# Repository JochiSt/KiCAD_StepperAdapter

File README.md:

# KiCAD_StepperAdapter
Adapter from stepper motor driver to screw terminals. 

Using the pinout of a A4988 module. Basically the pins of 
* step
* dir
* enable
* GND
are connected to a 4 pin screw terminal.

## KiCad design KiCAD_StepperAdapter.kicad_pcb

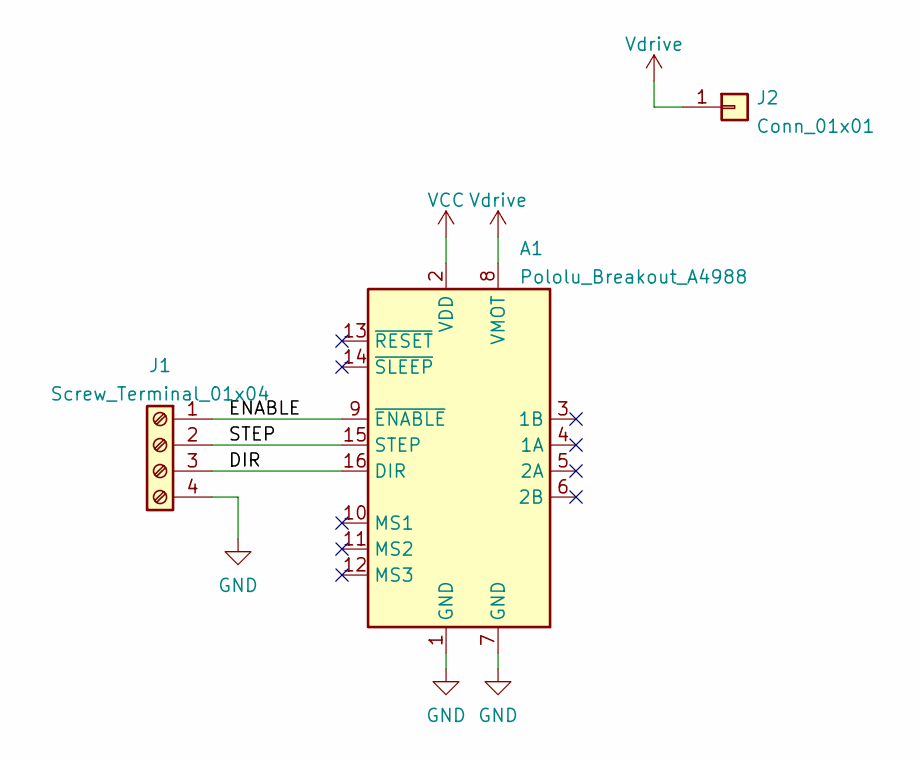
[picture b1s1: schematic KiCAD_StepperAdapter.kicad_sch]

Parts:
A1: Pololu_Breakout_A4988; Pololu_Breakout-16_15.2x20.3mm
J1: Screw_Terminal_01x04; TerminalBlock_Phoenix_MKDS-1,5-4-5.08_1x04_P5.08mm_Horizont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
J2: Conn_01x01; PinHeader_1x01_P2.54mm_Vertical

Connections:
/DIR: A1.16 (DIR), J1.3
/ENABLE: A1.9 (~ENABLE), J1.1
/STEP: A1.15 (STEP), J1.2
GND: A1.1 (GND), A1.7 (GND), J1.4
VCC: A1.2 (VDD)
Vdrive: A1.8 (VMOT), J2.1

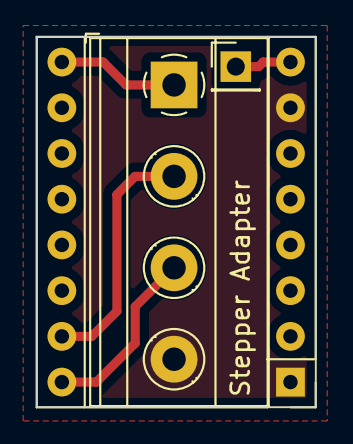
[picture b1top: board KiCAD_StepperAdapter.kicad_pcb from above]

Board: 2 copper layers, 15.5 x 20.6 mm, 3 parts (0 on the bottom side), 5 nets.

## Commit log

2022-07-08 added gitignore for KiCAD backups
2022-07-08 ignore fp-info-cache
2022-07-08 added first version of PCB
